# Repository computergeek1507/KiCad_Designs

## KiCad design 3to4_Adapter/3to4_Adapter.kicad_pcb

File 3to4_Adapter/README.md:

# Copyright and Disclaimer
Copyright: Scott Hanson

This documentation describes Open Hardware and is licensed under the CERN OHL v. 1.2.

You may redistribute and modify this documentation under the terms of the CERN OHL v.1.2. (http://ohwr.org/cernohl). This documentation is distributed WITHOUT ANY EXPRESS OR IMPLIED WARRANTY, INCLUDING OF MERCHANTABILITY, SATISFACTORY QUALITY AND FITNESS FOR A PARTICULAR PURPOSE. Please see the CERN OHL v.1.2 for applicable conditions

# 3 to 4 Adapter

Adapter to use Falcon v3 Expansions with the Falcon v4 Controllers. Open source applications were used to create this controller. [KiCad](http://kicad-pcb.org/) was used for the PCB design, and [LibreOffice](https://www.libreoffice.org/) for the documentation.

To order your own PCB upload the gerber.zip file to your favorite PCB manufacture of choice, I personally use [jlcpcb.com](https://jlcpcb.com/).

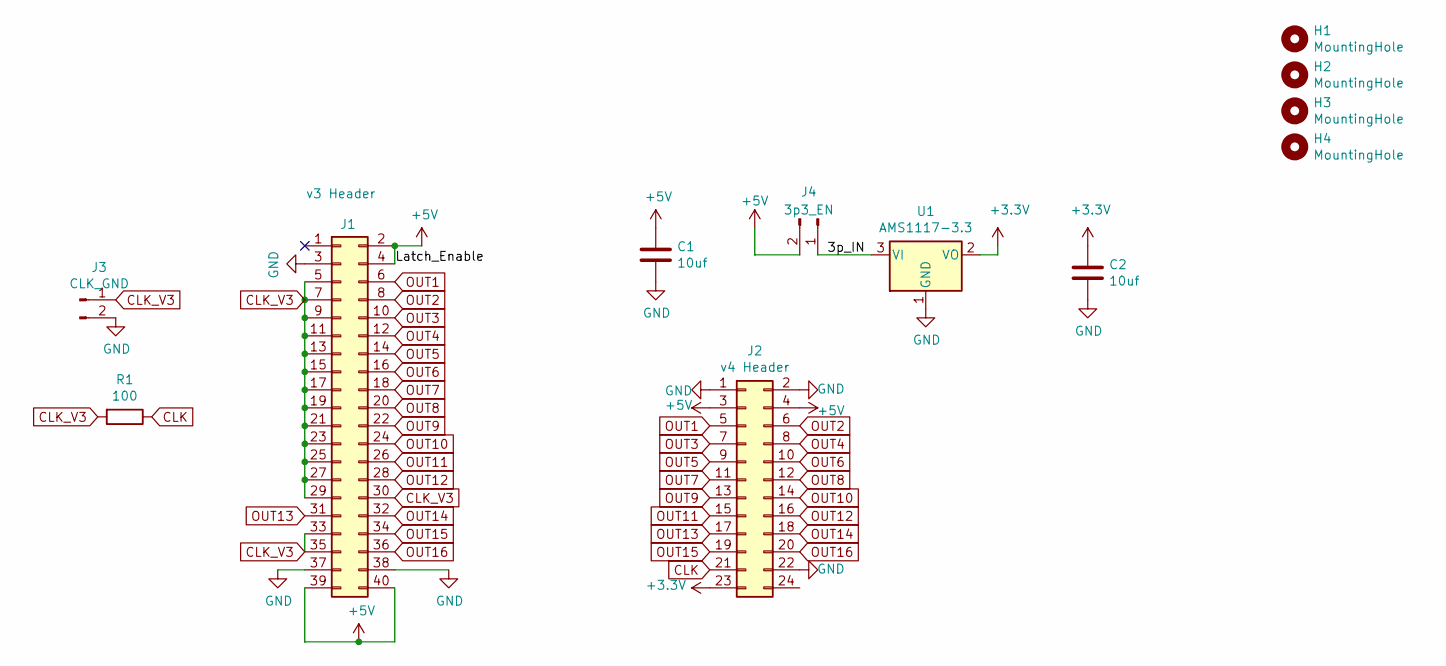
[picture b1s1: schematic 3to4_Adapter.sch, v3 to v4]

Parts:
C1, C2: 10uf; CP_Radial_D5.0mm_P2.00mm; MPN 35ZLG10MEFC5X7; Digi-Key_PN 1189-4000-ND
H1, H2, H3, H4: MountingHole; MountingHole_4.3mm_M4
J1: v3 Header; IDC-Header_2x20_P2.54mm_Vertical; MPN SBH11-PBPC-D20-ST-BK; Digi-Key_PN S9175-ND
J2: v4 Header; OST_302-S241; MPN 302-S241; Digi-Key_PN ED10525-ND
J3: CLK_GND; PinHeader_1x02_P2.54mm_Vertical; MPN 61300211121; Digi-Key_PN 732-5315-ND
J4: 3p3_EN; PinHeader_1x02_P2.54mm_Vertical; MPN 61300211121; Digi-Key_PN 732-5315-ND
R1: 100; R_Axial_DIN0207_L6.3mm_D2.5mm_P7.62mm_Horizontal; MPN CF14JT10K0; Digi-Key_PN CF14JT10K0TR-ND
U1: AMS1117-3.3; SOT-223-3_TabPin2; MPN AP2111H-3.3TRG1; Digi-Key_PN AP2111H-3.3TRG1DICT-ND

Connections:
+3V3: C2.1, J2.23, U1.2 (VO)
+5V: C1.1, J1.2, J1.4, J1.39, J1.40, J2.3, J2.4, J4.2
/3p_IN: J4.1, U1.3 (VI)
CLK: J2.21, R1.1
CLK_V3: J1.5, J1.7, J1.9, J1.11, J1.13, J1.15, J1.17, J1.19, J1.21, J1.23, J1.25, J1.27, J1.29, J1.30, J1.33, J1.35, J3.1, R1.2
GND: C1.2, C2.2, J1.3, J1.37, J1.38, J2.1, J2.2, J2.22, J3.2, U1.1 (GND)
OUT1: J1.6, J2.5
OUT2: J1.8, J2.6
OUT3: J1.10, J2.7
OUT4: J1.12, J2.8
OUT5: J1.14, J2.9
OUT6: J1.16, J2.10
OUT7: J1.18, J2.11
OUT8: J1.20, J2.12
OUT9: J1.22, J2.13
OUT10: J1.24, J2.14
OUT11: J1.26, J2.15
OUT12: J1.28, J2.16
OUT13: J1.31, J2.17
OUT14: J1.32, J2.18
OUT15: J1.34, J2.19
OUT16: J1.36, J2.20

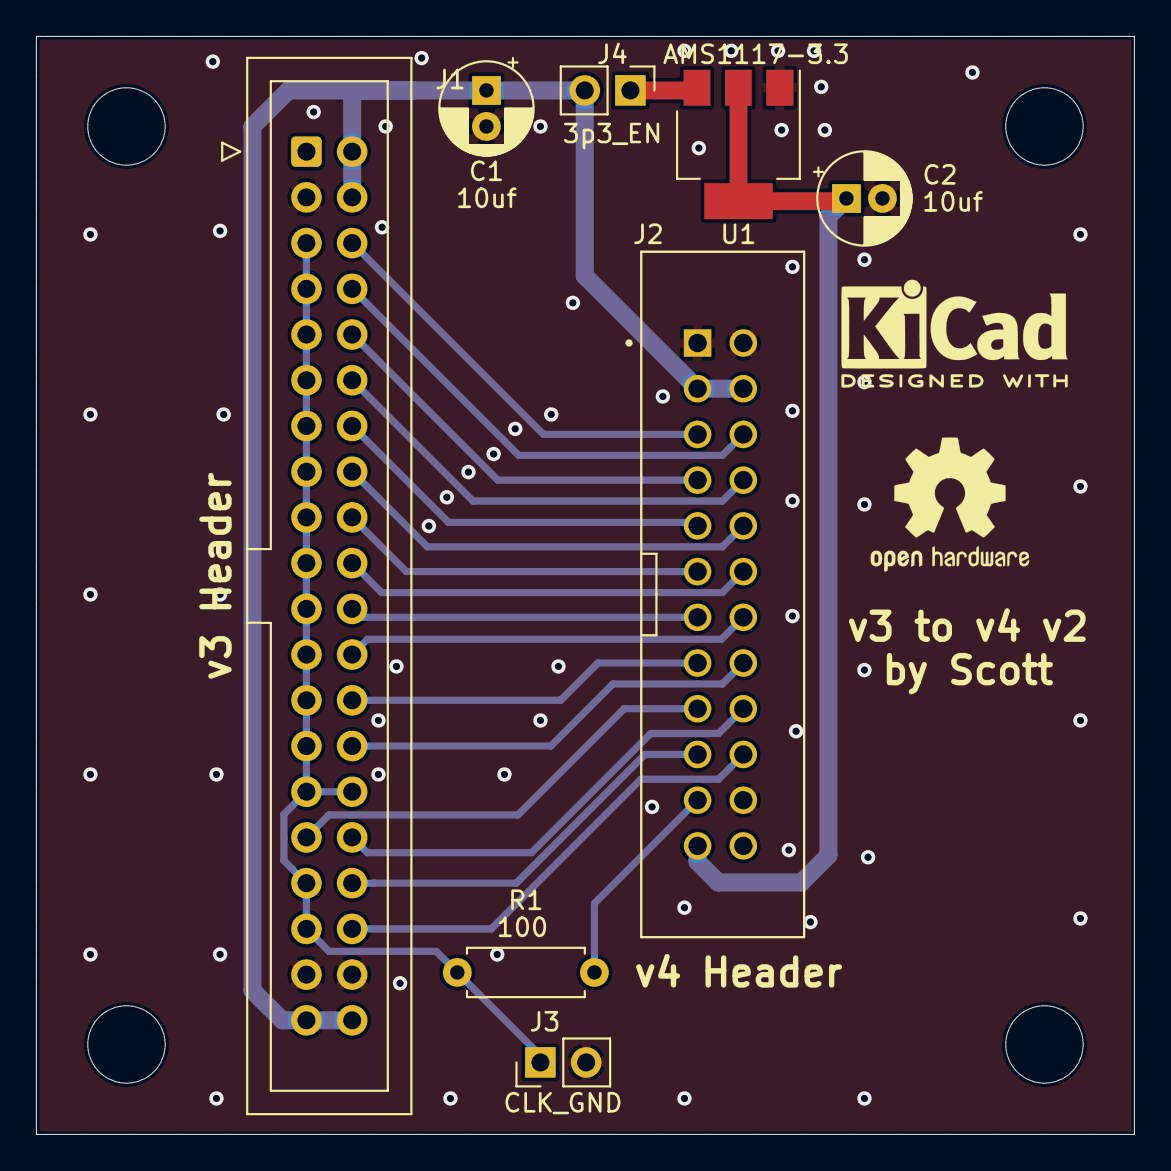
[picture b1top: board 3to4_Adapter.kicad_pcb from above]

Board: 2 copper layers, 61.0 x 61.0 mm, 12 parts (0 on the bottom side), 22 nets.

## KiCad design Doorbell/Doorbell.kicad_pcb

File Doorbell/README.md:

# Copyright and Disclaimer
Copyright: Scott Hanson

This documentation describes Open Hardware and is licensed under the CERN OHL v. 1.2.

You may redistribute and modify this documentation under the terms of the CERN OHL v.1.2. (http://ohwr.org/cernohl). This documentation is distributed WITHOUT ANY EXPRESS OR IMPLIED WARRANTY, INCLUDING OF MERCHANTABILITY, SATISFACTORY QUALITY AND FITNESS FOR A PARTICULAR PURPOSE. Please see the CERN OHL v.1.2 for applicable conditions

# Doorbell

ESP8266 Doorbell Adapter, measures doorbell switch voltage and sends notifications to openHAB. The design was made with all through hole components for easy assembly by most users. Open source applications were used to create this controller. [KiCad](http://kicad-pcb.org/) was used for the PCB design, and [LibreOffice](https://www.libreoffice.org/) for the documentation.

To order your own PCB upload the gerber.zip file to your favorite PCB manufacture of choice, I personally use [jlcpcb.com](https://jlcpcb.com/).

## [Arduino Source Code](https://raw.githubusercontent.com/computergeek1507/arduino/master/ESPMQTT/ESPMQTT.ino)

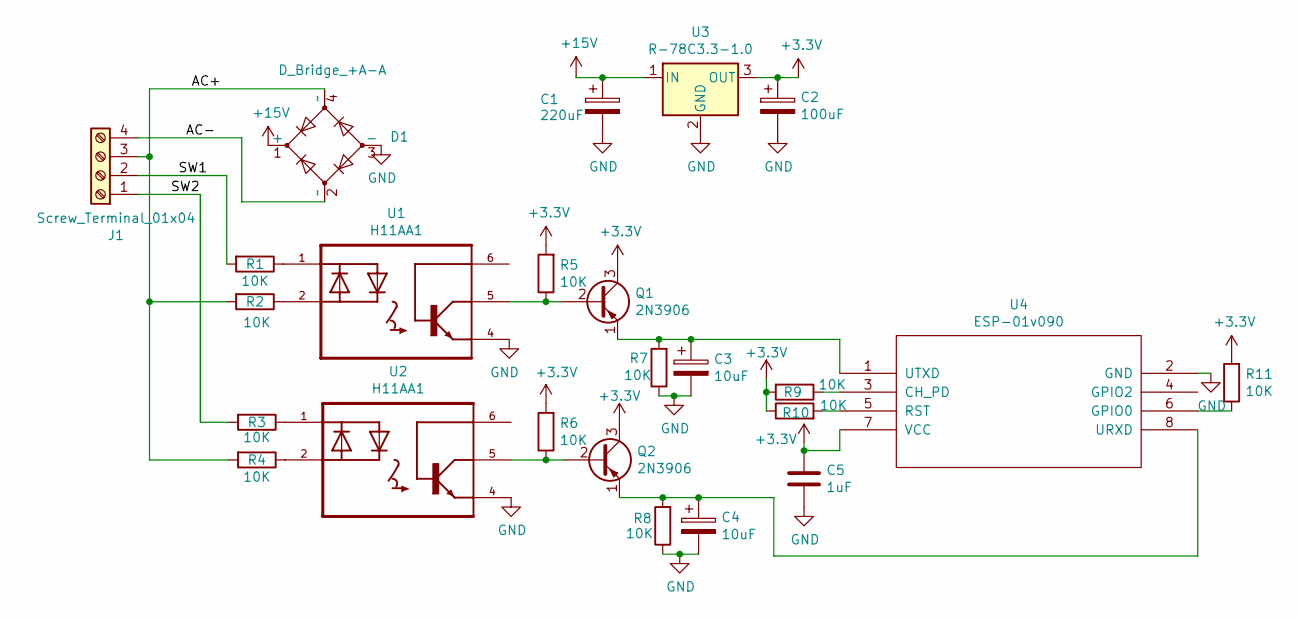
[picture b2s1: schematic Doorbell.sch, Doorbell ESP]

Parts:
C1: 220uF; CP_Radial_D10.0mm_P5.00mm; Manufacture PN ECA-1HM221; Digikey PN P5183-ND
C2: 100uF; CP_Radial_D6.3mm_P2.50mm; Manufacture PN 35ZLH100MEFC6.3X11; Digikey PN 1189-1300-ND
C3, C4: 10uF; CP_Radial_D5.0mm_P2.50mm; Manufacture PN UVR1H100MDD; Digikey PN 493-1103-ND
C5: 1uF; CP_Radial_D5.0mm_P2.50mm; Manufacture PN ESK105M050AC3AA; Digikey PN 399-6596-ND
D1: D_Bridge_+A-A; Diode_Bridge_Round_D8.9mm; Manufacture PN W04G-E4/51; Digikey PN W04G-E4/51GI-ND
J1: Screw_Terminal_01x04; TerminalBlock_Phoenix_MKDS-1,5-4_1x04_P5.00mm_Horizontal; Manufacture PN 1935187; Digikey PN 277-1579-ND
Q1, Q2: 2N3906; TO-92; Manufacture PN 2N3906BU; Digikey PN 2N3906FS-ND
R1, R2, R3, R4, R5, R6, R7, R8, R9, R10, R11: 10K; R_Axial_DIN0204_L3.6mm_D1.6mm_P1.90mm_Vertical; Manufacture PN CF14JT10K0; Digikey PN CF14JT10K0CT-ND
U1, U2: H11AA1; DIP762W50P254L730H410Q6; Manufacture PN H11AA1-X006; Digikey PN H11AA1-X006-ND
U3: R-78C3.3-1.0; Converter_DCDC_RECOM_R-78E-0.5_THT; Manufacture PN OKI-78SR-3.3/1.5-W36-C; Digikey PN 811-2195-5-ND
U4: ESP-01v090; ESP-01; Manufacture PN WRL-13678; Digikey PN 1568-1235-ND

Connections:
+3V3: C2.1, C5.1, Q1.3 (C), Q2.3 (C), R5.2, R6.2, R9.2, R10.1, R11.2, U3.3 (OUT), U4.7 (VCC)
+15V: C1.1, D1.1 (+), U3.1 (IN)
/AC+: D1.4 (~~), J1.3, R2.2, R4.2
/AC-: D1.2 (~~), J1.4
/SW1: J1.2, R1.2
/SW2: J1.1, R3.2
GND: C1.2, C2.2, C3.2, C4.2, C5.2, D1.3 (-), R7.1, R8.1, U1.4 (E), U2.4 (E), U3.2 (GND), U4.2 (GND)
unnamed: C3.1, Q1.1 (E), R7.2, U4.1 (UTXD)
unnamed: C4.1, Q2.1 (E), R8.2, U4.8 (URXD)
unnamed: Q1.2 (B), R5.1, U1.5 (C)
unnamed: Q2.2 (B), R6.1, U2.5 (C)
unnamed: R1.1, U1.1 (A/C)
unnamed: R2.1, U1.2 (C/A)
unnamed: R3.1, U2.1 (A/C)
unnamed: R4.1, U2.2 (C/A)
unnamed: R9.1, U4.3 (CH_PD)
unnamed: R10.2, U4.5 (RST)
unnamed: R11.1, U4.6 (GPIO0)

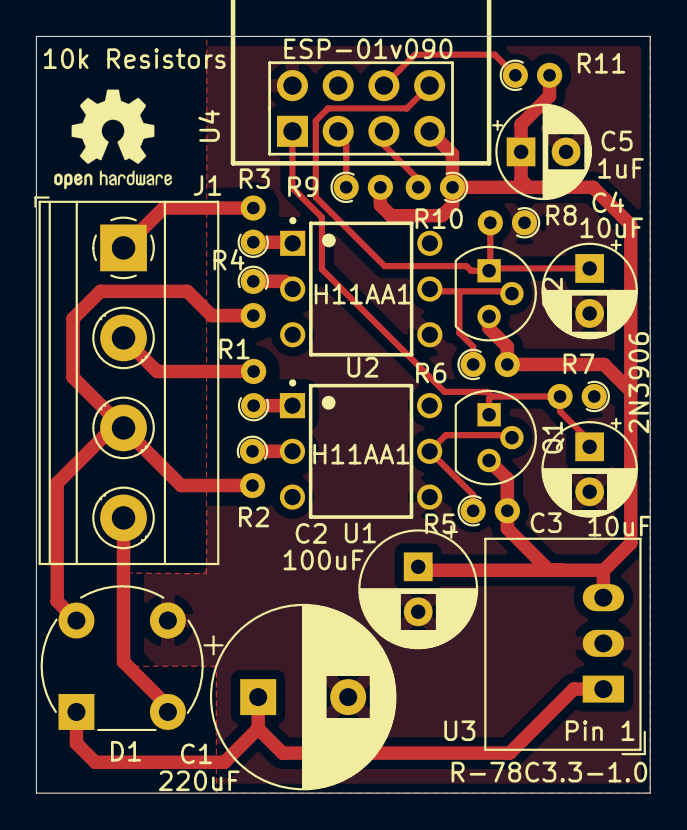
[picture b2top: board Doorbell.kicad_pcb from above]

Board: 2 copper layers, 34.1 x 42.0 mm, 24 parts (0 on the bottom side), 18 nets.

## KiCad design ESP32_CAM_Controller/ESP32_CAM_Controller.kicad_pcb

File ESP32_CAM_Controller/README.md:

# Copyright and Disclaimer
Copyright: Scott Hanson

This documentation describes Open Hardware and is licensed under the CERN OHL v. 1.2.

You may redistribute and modify this documentation under the terms of the CERN OHL v.1.2. (http://ohwr.org/cernohl). This documentation is distributed WITHOUT ANY EXPRESS OR IMPLIED WARRANTY, INCLUDING OF MERCHANTABILITY, SATISFACTORY QUALITY AND FITNESS FOR A PARTICULAR PURPOSE. Please see the CERN OHL v.1.2 for applicable conditions

# ESP32 CAM Controller

4 port Controller breakout for ESP32 CAM Moduke design was made with all through hole components for easy assembly by most users. Open source applications were used to create this controller. [KiCad](http://kicad-pcb.org/) was used for the PCB design, and [LibreOffice](https://www.libreoffice.org/) for the documentation.

To order your own PCB upload the gerber.zip file to your favorite PCB manufacture of choice, I personally use [jlcpcb.com](https://jlcpcb.com/).

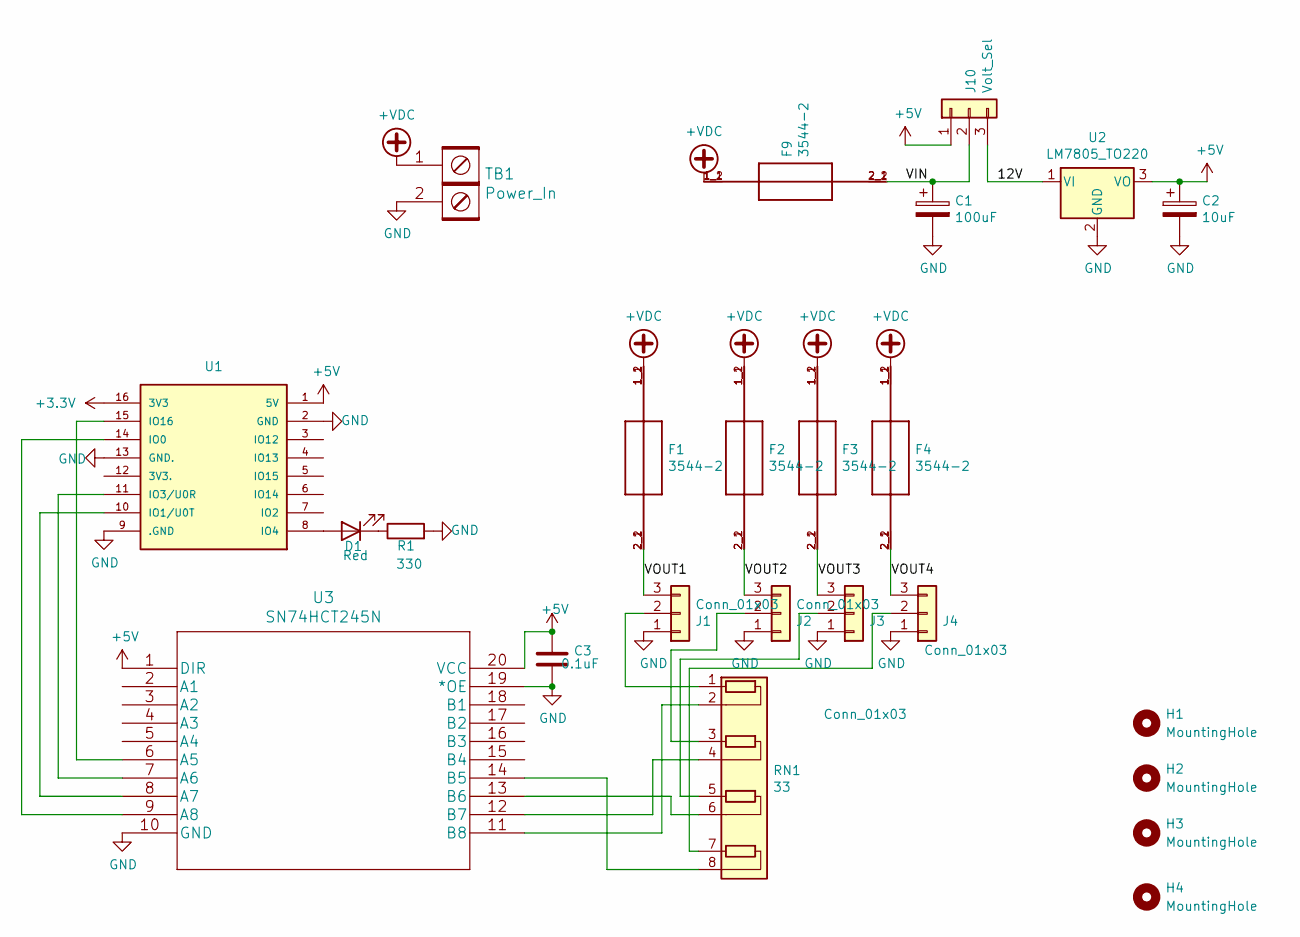
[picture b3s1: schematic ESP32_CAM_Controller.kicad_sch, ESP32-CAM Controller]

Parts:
C1: 100uF; CP_Radial_D8.0mm_P3.50mm
C2: 10uF; CP_Radial_D5.0mm_P2.00mm
C3: 0.1uF; C_Rect_L7.0mm_W2.0mm_P5.00mm
D1: Red; LED_D3.0mm
F1, F2, F3, F4, F9: 3544-2; FUSE_3544-2
H1, H2, H3, H4: MountingHole; MountingHole_3.5mm
J1, J2, J3, J4: Conn_01x03; PhoenixContact_MCV_1,5_3-G-3.5_1x03_P3.50mm_Vertical
J10: Volt_Sel; PinHeader_1x03_P2.54mm_Vertical
R1: 330; R_Axial_DIN0207_L6.3mm_D2.5mm_P7.62mm_Horizontal
RN1: 33; R_Array_SIP8
TB1: Power_In; BARRIER_BLOCK_1ROW_2POS_P8.26MM
U1: ESP32-CAM
U2: LM7805_TO220; TO-220-3_Horizontal_TabDown
U3: SN74HCT245N

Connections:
+3V3: U1.16 (3V3)
+5V: C2.1, C3.1, J10.1, U1.1 (5V), U2.3 (VO), U3.1 (DIR), U3.20 (VCC)
+VDC: F1.1_1 (1), F1.1_2 (1), F2.1_1 (1), F2.1_2 (1), F3.1_1 (1), F3.1_2 (1), F4.1_1 (1), F4.1_2 (1), F9.1_1 (1), F9.1_2 (1), TB1.1
/12V: J10.3, U2.1 (VI)
/VIN: C1.1, F9.2_1 (2), F9.2_2 (2), J10.2
/VOUT1: F1.2_1 (2), F1.2_2 (2), J1.3
/VOUT2: F2.2_1 (2), F2.2_2 (2), J2.3
/VOUT3: F3.2_1 (2), F3.2_2 (2), J3.3
/VOUT4: F4.2_1 (2), F4.2_2 (2), J4.3
GND: C1.2, C2.2, C3.2, J1.1, J2.1, J3.1, J4.1, R1.2, TB1.2, U1.2 (GND), U1.9 (.GND), U1.13 (GND.), U2.2 (GND), U3.10 (GND), U3.19 (*OE)
unnamed: D1.1 (K), R1.1
unnamed: D1.2 (A), U1.8 (IO4)
unnamed: J1.2, RN1.1 (R1.1)
unnamed: J2.2, RN1.3 (R2.1)
unnamed: J3.2, RN1.5 (R3.1)
unnamed: J4.2, RN1.7 (R4.1)
unnamed: U1.15 (IO16), U3.6 (A5)
unnamed: U1.11 (IO3/U0R), U3.7 (A6)
unnamed: U1.10 (IO1/U0T), U3.8 (A7)
unnamed: U1.14 (IO0), U3.9 (A8)
unnamed: RN1.2 (R1.2), U3.11 (B8)
unnamed: RN1.4 (R2.2), U3.12 (B7)
unnamed: RN1.6 (R3.2), U3.13 (B6)
unnamed: RN1.8 (R4.2), U3.14 (B5)

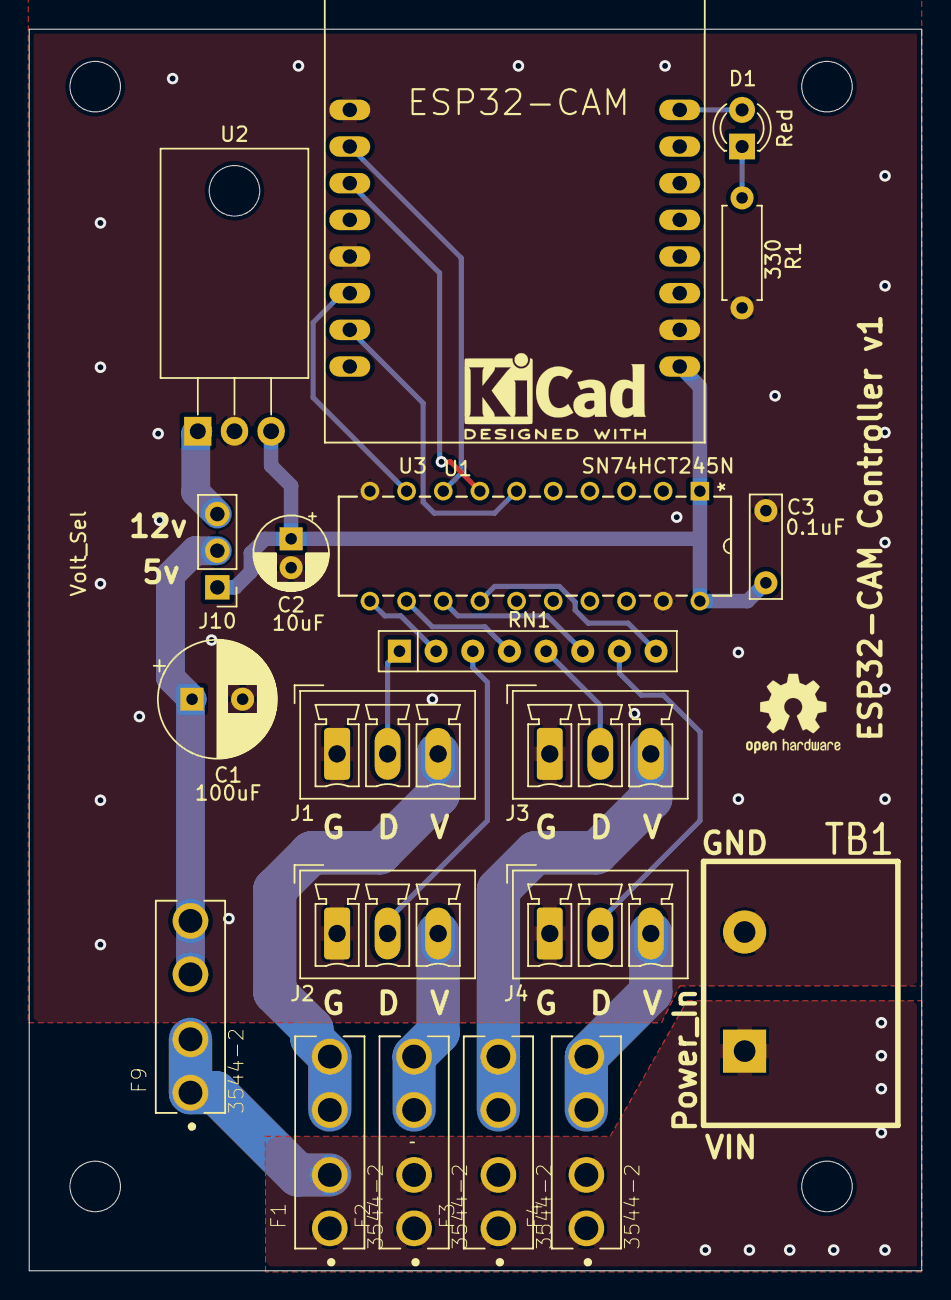
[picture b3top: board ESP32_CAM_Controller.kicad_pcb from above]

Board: 2 copper layers, 61.8 x 86.0 mm, 24 parts (0 on the bottom side), 23 nets.

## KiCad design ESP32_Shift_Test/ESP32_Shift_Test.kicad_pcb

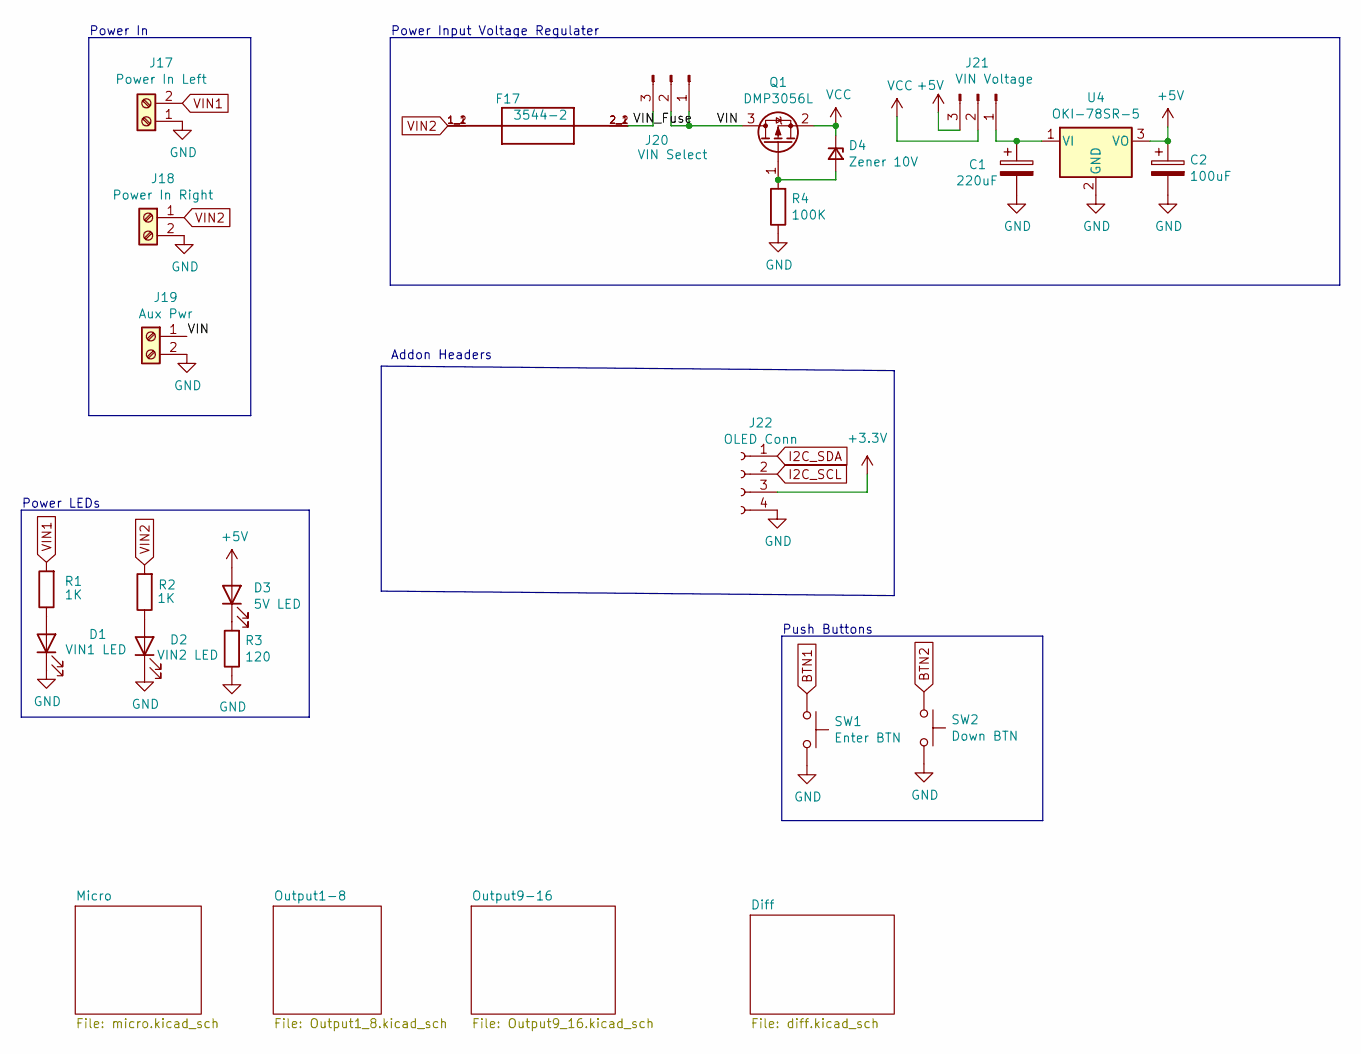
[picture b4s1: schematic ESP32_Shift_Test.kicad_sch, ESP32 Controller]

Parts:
C1: 220uF; CP_Radial_D10.0mm_P5.00mm; MPN ECA-1HM221; Digi-Key_PN P5183-ND
C2: 100uF; CP_Elec_6.3x5.4_Nichicon; MPN UWX1C101MCL1GB; Digi-Key_PN 493-2105-1-ND
D1: VIN1 LED; LED_0603_1608Metric_Pad1.05x0.95mm_HandSolder; MPN LTST-C171GKT; Digi-Key_PN 160-1423-1-ND
D2: VIN2 LED; LED_0603_1608Metric_Pad1.05x0.95mm_HandSolder; MPN LTST-C171GKT; Digi-Key_PN 160-1423-1-ND
D3: 5V LED; LED_0603_1608Metric_Pad1.05x0.95mm_HandSolder; MPN LTST-C171GKT; Digi-Key_PN 160-1423-1-ND
D4: Zener 10V; D_SOD-123; MPN MMSZ5240B-7-F; Digi-Key_PN MMSZ5240B-FDICT-ND
F17: 3544-2; FUSE_3544-2; MPN 3544-2; Digi-Key_PN 36-3544-2-ND
J17: Power In Left; BARRIER_BLOCK_1ROW_2POS_P9.5MM; MPN OSTYK51102030; Digi-Key_PN ED2953-ND
J18: Power In Right; BARRIER_BLOCK_1ROW_2POS_P9.5MM; MPN OSTYK51102030; Digi-Key_PN ED2953-ND
J19: Aux Pwr; PHOENIX_MKDS1_2-3.81; MPN 1727010; Digi-Key_PN 277-1947-ND
J20: VIN Select; PinHeader_1x03_P2.54mm_Vertical; MPN 61300311121; Digi-Key_PN 732-5316-ND
J21: VIN Voltage; PinHeader_1x03_P2.54mm_Vertical; MPN 61300311121; Digi-Key_PN 732-5316-ND
J22: OLED Conn; PinSocket_1x04_P2.54mm_Vertical; MPN PPTC041LFBN-RC; Digi-Key_PN S7002-ND
Q1: DMP3056L; SOT-23; MPN DMP3056L-7; Digi-Key_PN DMP3056L-7DICT-ND
R1, R2: 1K; R_0603_1608Metric_Pad0.98x0.95mm_HandSolder; MPN RNCP0805FTD1K00; Digi-Key_PN RNCP0805FTD1K00CT-ND
R3: 120; R_0603_1608Metric_Pad0.98x0.95mm_HandSolder; MPN RC0805JR-07120RL; Digi-Key_PN 311-120ARCT-ND
R4: 100K; R_0603_1608Metric_Pad0.98x0.95mm_HandSolder; MPN RC0805FR-07100KL; Digi-Key_PN 311-100KCRCT-ND
SW1: Enter BTN; SW_Push_1P1T_NO_6x6mm_H9.5mm; MPN PTS645SL50SMTR92 LFS; Digi-Key_PN CKN9088CT-ND
SW2: Down BTN; SW_Push_1P1T_NO_6x6mm_H9.5mm; MPN PTS645SL50SMTR92 LFS; Digi-Key_PN CKN9088CT-ND
U4: OKI-78SR-5; Converter_DCDC_muRata_OKI-78SR_Horizontal; MPN OKI-78SR-5/1.5-W36-C; Digi-Key_PN 811-2196-5-ND

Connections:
+3V3: J22.3; also elsewhere on the board
+5V: C2.1, D3.2 (A), J21.3, U4.3 (VO); also elsewhere on the board
/VIN: J19.1, J20.1, J20.2, Q1.3 (D)
/VIN_Fuse: F17.2_1 (2), F17.2_2 (2), J20.3
BTN1: SW1.1; also elsewhere on the board
BTN2: SW2.1; also elsewhere on the board
GND: C1.2, C2.2, D1.1 (K), D2.1 (K), J17.1, J18.2, J19.2, J22.4, R3.1, R4.1, SW1.2, SW2.2, U4.2 (GND); also elsewhere on the board
I2C_SCL: J22.2; also elsewhere on the board
I2C_SDA: J22.1; also elsewhere on the board
unnamed: C1.1, J21.1, U4.1 (VI)
unnamed: D1.2 (A), R1.1
unnamed: D2.2 (A), R2.1
unnamed: D3.1 (K), R3.2
unnamed: D4.2 (A), Q1.1 (G), R4.2
VCC: D4.1 (K), J21.2, Q1.2 (S)
VIN1: J17.2, R1.2; also elsewhere on the board
VIN2: F17.1_1 (1), F17.1_2 (1), J18.1, R2.2; also elsewhere on the board

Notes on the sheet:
Power Input Voltage Regulater
Power In
Power LEDs
Push Buttons
Addon Headers

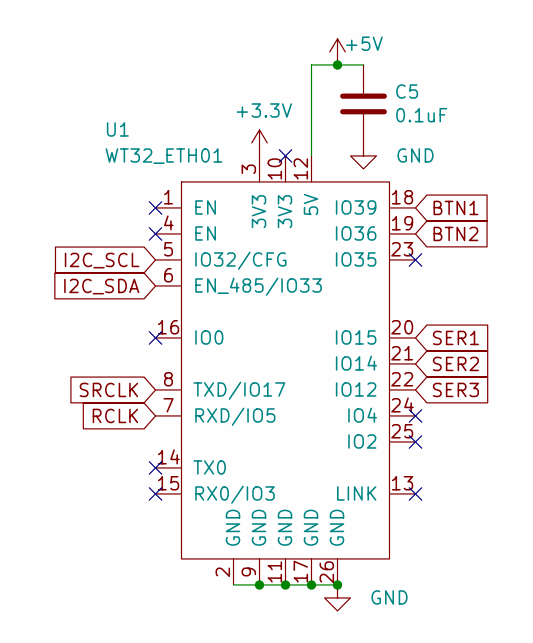
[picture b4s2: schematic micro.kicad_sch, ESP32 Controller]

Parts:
C5: 0.1uF; C_0603_1608Metric_Pad1.08x0.95mm_HandSolder; MPN CL21F104ZBCNNNC; Digi-Key_PN 1276-1007-1-ND
U1: WT32_ETH01

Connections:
+3V3: U1.3 (3V3); also elsewhere on the board
+5V: C5.1, U1.12 (5V); also elsewhere on the board
BTN1: U1.18 (IO39); also elsewhere on the board
BTN2: U1.19 (IO36); also elsewhere on the board
GND: C5.2, U1.2 (GND), U1.9 (GND), U1.11 (GND), U1.17 (GND), U1.26 (GND); also elsewhere on the board
I2C_SCL: U1.5 (IO32/CFG); also elsewhere on the board
I2C_SDA: U1.6 (EN_485/IO33); also elsewhere on the board
RCLK: U1.7 (RXD/IO5); also elsewhere on the board
SER1: U1.20 (IO15); also elsewhere on the board
SER2: U1.21 (IO14); also elsewhere on the board
SER3: U1.22 (IO12); also elsewhere on the board
SER4: U1.24 (IO4)
SRCLK: U1.8 (TXD/IO17); also elsewhere on the board

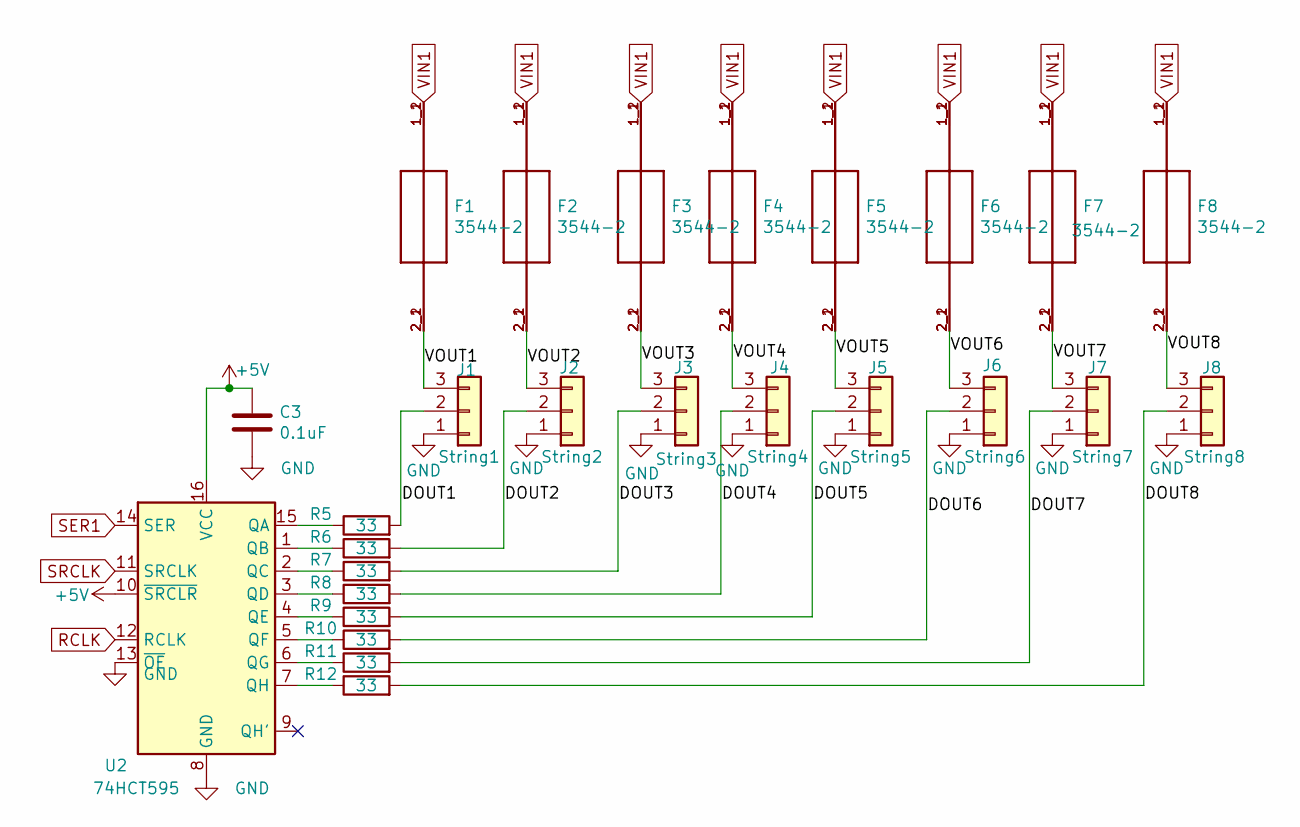
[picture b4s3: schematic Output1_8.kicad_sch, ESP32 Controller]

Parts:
C3: 0.1uF; C_0603_1608Metric_Pad1.08x0.95mm_HandSolder; MPN CL21F104ZBCNNNC; Digi-Key_PN 1276-1007-1-ND
F1, F2, F3, F4, F5, F6, F7, F8: 3544-2; FUSE_3544-2; MPN 3544-2; Digi-Key_PN 36-3544-2-ND
J1: String1; PhoenixContact_MCV_1,5_3-G-3.5_1x03_P3.50mm_Vertical; MPN 1843619/OSTTJ0311530; Digi-Key_PN 277-5737-ND/ED10555-ND
J2: String2; PhoenixContact_MCV_1,5_3-G-3.5_1x03_P3.50mm_Vertical; MPN 1843619/OSTTJ0311530; Digi-Key_PN 277-5737-ND/ED10555-ND
J3: String3; PhoenixContact_MCV_1,5_3-G-3.5_1x03_P3.50mm_Vertical; MPN 1843619/OSTTJ0311530; Digi-Key_PN 277-5737-ND/ED10555-ND
J4: String4; PhoenixContact_MCV_1,5_3-G-3.5_1x03_P3.50mm_Vertical; MPN 1843619/OSTTJ0311530; Digi-Key_PN 277-5737-ND/ED10555-ND
J5: String5; PhoenixContact_MCV_1,5_3-G-3.5_1x03_P3.50mm_Vertical; MPN 1843619/OSTTJ0311530; Digi-Key_PN 277-5737-ND/ED10555-ND
J6: String6; PhoenixContact_MCV_1,5_3-G-3.5_1x03_P3.50mm_Vertical; MPN 1843619/OSTTJ0311530; Digi-Key_PN 277-5737-ND/ED10555-ND
J7: String7; PhoenixContact_MCV_1,5_3-G-3.5_1x03_P3.50mm_Vertical; MPN 1843619/OSTTJ0311530; Digi-Key_PN 277-5737-ND/ED10555-ND
J8: String8; PhoenixContact_MCV_1,5_3-G-3.5_1x03_P3.50mm_Vertical; MPN 1843619/OSTTJ0311530; Digi-Key_PN 277-5737-ND/ED10555-ND
R5, R6, R7, R8, R9, R10, R11, R12: 33; R_0603_1608Metric_Pad0.98x0.95mm_HandSolder; MPN CN34J330CT; LCSC C23140
U2: 74HCT595; SOIC-16_3.9x9.9mm_P1.27mm

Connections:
+5V: C3.1, U2.10 (~SRCLR), U2.16 (VCC); also elsewhere on the board
/Output1-8/DOUT1: J1.2, R5.2
/Output1-8/DOUT2: J2.2, R6.2
/Output1-8/DOUT3: J3.2, R7.2
/Output1-8/DOUT4: J4.2, R8.2
/Output1-8/DOUT5: J5.2, R9.2
/Output1-8/DOUT6: J6.2, R10.2
/Output1-8/DOUT7: J7.2, R11.2
/Output1-8/DOUT8: J8.2, R12.2
/Output1-8/VOUT1: F1.2_1 (2), F1.2_2 (2), J1.3
/Output1-8/VOUT2: F2.2_1 (2), F2.2_2 (2), J2.3
/Output1-8/VOUT3: F3.2_1 (2), F3.2_2 (2), J3.3
/Output1-8/VOUT4: F4.2_1 (2), F4.2_2 (2), J4.3
/Output1-8/VOUT5: F5.2_1 (2), F5.2_2 (2), J5.3
/Output1-8/VOUT6: F6.2_1 (2), F6.2_2 (2), J6.3
/Output1-8/VOUT7: F7.2_1 (2), F7.2_2 (2), J7.3
/Output1-8/VOUT8: F8.2_1 (2), F8.2_2 (2), J8.3
GND: C3.2, J1.1, J2.1, J3.1, J4.1, J5.1, J6.1, J7.1, J8.1, U2.8 (GND), U2.13 (~OE); also elsewhere on the board
unnamed: R5.1, U2.15 (QA)
unnamed: R6.1, U2.1 (QB)
unnamed: R7.1, U2.2 (QC)
unnamed: R8.1, U2.3 (QD)
unnamed: R9.1, U2.4 (QE)
unnamed: R10.1, U2.5 (QF)
unnamed: R11.1, U2.6 (QG)
unnamed: R12.1, U2.7 (QH)
RCLK: U2.12 (RCLK); also elsewhere on the board
SER1: U2.14 (SER); also elsewhere on the board
SRCLK: U2.11 (SRCLK); also elsewhere on the board
VIN1: F1.1_1 (1), F1.1_2 (1), F2.1_1 (1), F2.1_2 (1), F3.1_1 (1), F3.1_2 (1), F4.1_1 (1), F4.1_2 (1), F5.1_1 (1), F5.1_2 (1), F6.1_1 (1), F6.1_2 (1), F7.1_1 (1), F7.1_2 (1), F8.1_1 (1), F8.1_2 (1); also elsewhere on the board

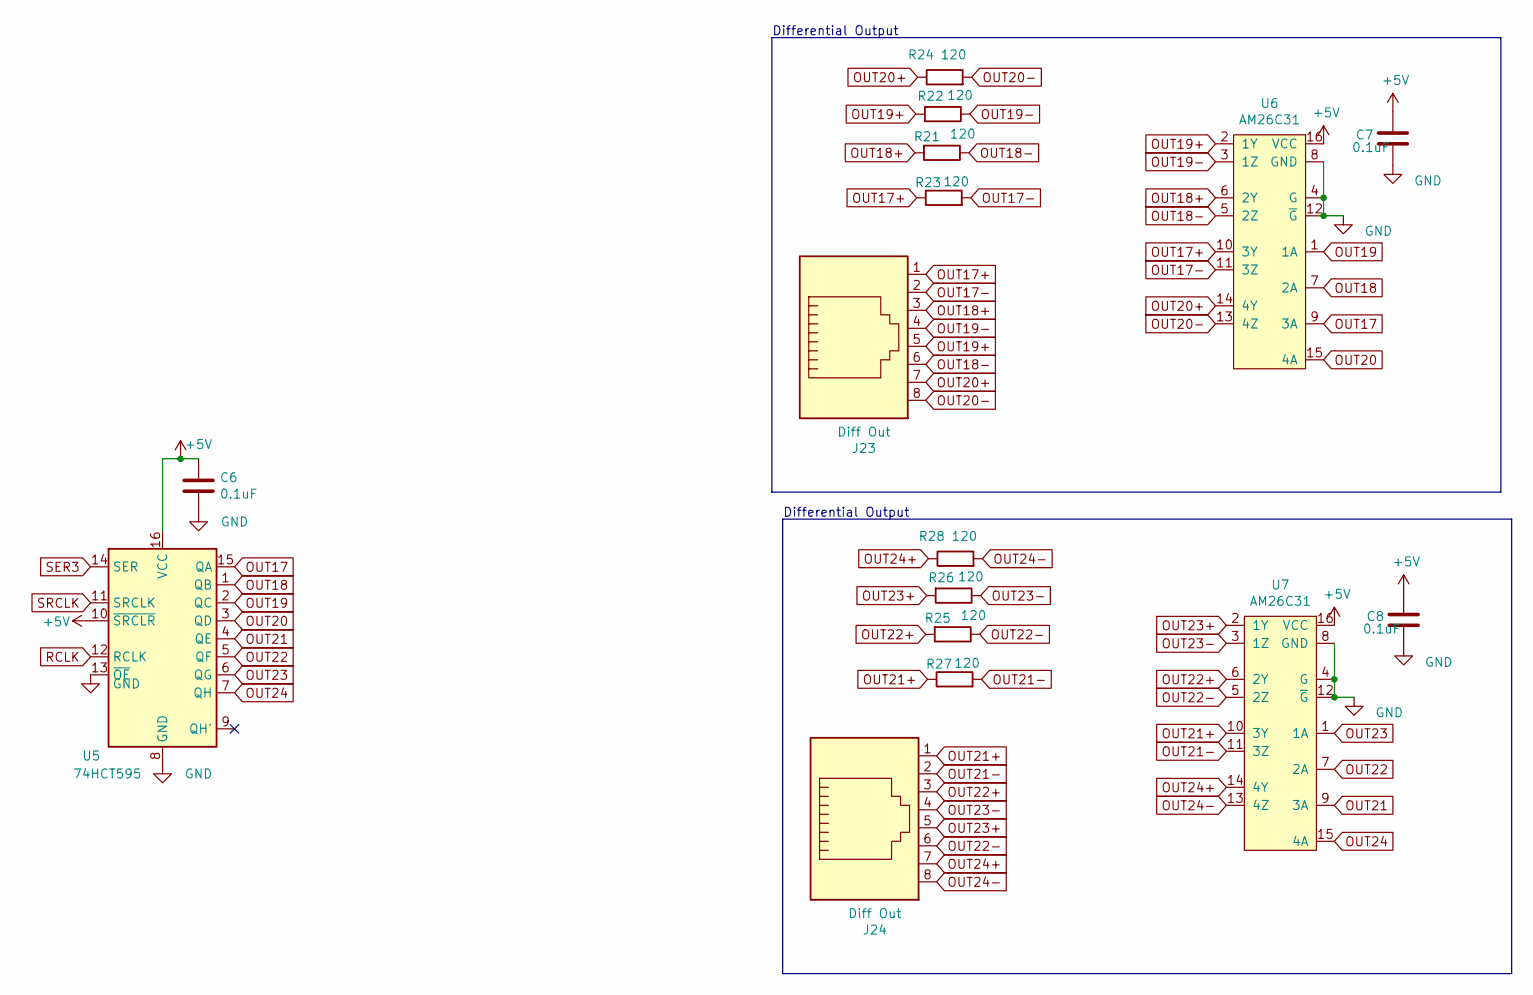
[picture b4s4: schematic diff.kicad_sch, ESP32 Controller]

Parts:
C6: 0.1uF; C_0603_1608Metric_Pad1.08x0.95mm_HandSolder; MPN CL21F104ZBCNNNC; Digi-Key_PN 1276-1007-1-ND
C7, C8: 0.1uF; C_0603_1608Metric_Pad1.08x0.95mm_HandSolder; MPN CL10B104KB8NNWC; Digi-Key_PN 1276-1935-2-ND
J23, J24: Diff Out; RJ45_Amphenol_54602-x08_Horizontal; MPN X05ADIWA1DY1022; Digi-Key_PN AE10392-ND
R21, R22, R23, R24, R25, R26, R27, R28: 120; R_0603_1608Metric_Pad0.98x0.95mm_HandSolder; MPN CRGCQ0603F120R; Digi-Key_PN A129677CT-ND
U5: 74HCT595; SOIC-16_3.9x9.9mm_P1.27mm
U6, U7: AM26C31; SOIC-16_3.9x9.9mm_P1.27mm; MPN AM26C31IDR; Farnell 4975637

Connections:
+5V: C6.1, C7.1, C8.1, U5.10 (~SRCLR), U5.16 (VCC), U6.16 (VCC), U7.16 (VCC); also elsewhere on the board
GND: C6.2, C7.2, C8.2, U5.8 (GND), U5.13 (~OE), U6.4 (G), U6.8 (GND), U6.12 (~G), U7.4 (G), U7.8 (GND), U7.12 (~G); also elsewhere on the board
OUT17: U5.15 (QA), U6.9 (3A)
OUT17+: J23.1, R23.1, U6.10 (3Y)
OUT17-: J23.2, R23.2, U6.11 (3Z)
OUT18: U5.1 (QB), U6.7 (2A)
OUT18+: J23.3, R21.2, U6.6 (2Y)
OUT18-: J23.6, R21.1, U6.5 (2Z)
OUT19: U5.2 (QC), U6.1 (1A)
OUT19+: J23.5, R22.2, U6.2 (1Y)
OUT19-: J23.4, R22.1, U6.3 (1Z)
OUT20: U5.3 (QD), U6.15 (4A)
OUT20+: J23.7, R24.1, U6.14 (4Y)
OUT20-: J23.8, R24.2, U6.13 (4Z)
OUT21: U5.4 (QE), U7.9 (3A)
OUT21+: J24.1, R27.1, U7.10 (3Y)
OUT21-: J24.2, R27.2, U7.11 (3Z)
OUT22: U5.5 (QF), U7.7 (2A)
OUT22+: J24.3, R25.2, U7.6 (2Y)
OUT22-: J24.6, R25.1, U7.5 (2Z)
OUT23: U5.6 (QG), U7.1 (1A)
OUT23+: J24.5, R26.2, U7.2 (1Y)
OUT23-: J24.4, R26.1, U7.3 (1Z)
OUT24: U5.7 (QH), U7.15 (4A)
OUT24+: J24.7, R28.1, U7.14 (4Y)
OUT24-: J24.8, R28.2, U7.13 (4Z)
RCLK: U5.12 (RCLK); also elsewhere on the board
SER3: U5.14 (SER); also elsewhere on the board
SRCLK: U5.11 (SRCLK); also elsewhere on the board

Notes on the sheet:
Differential Output

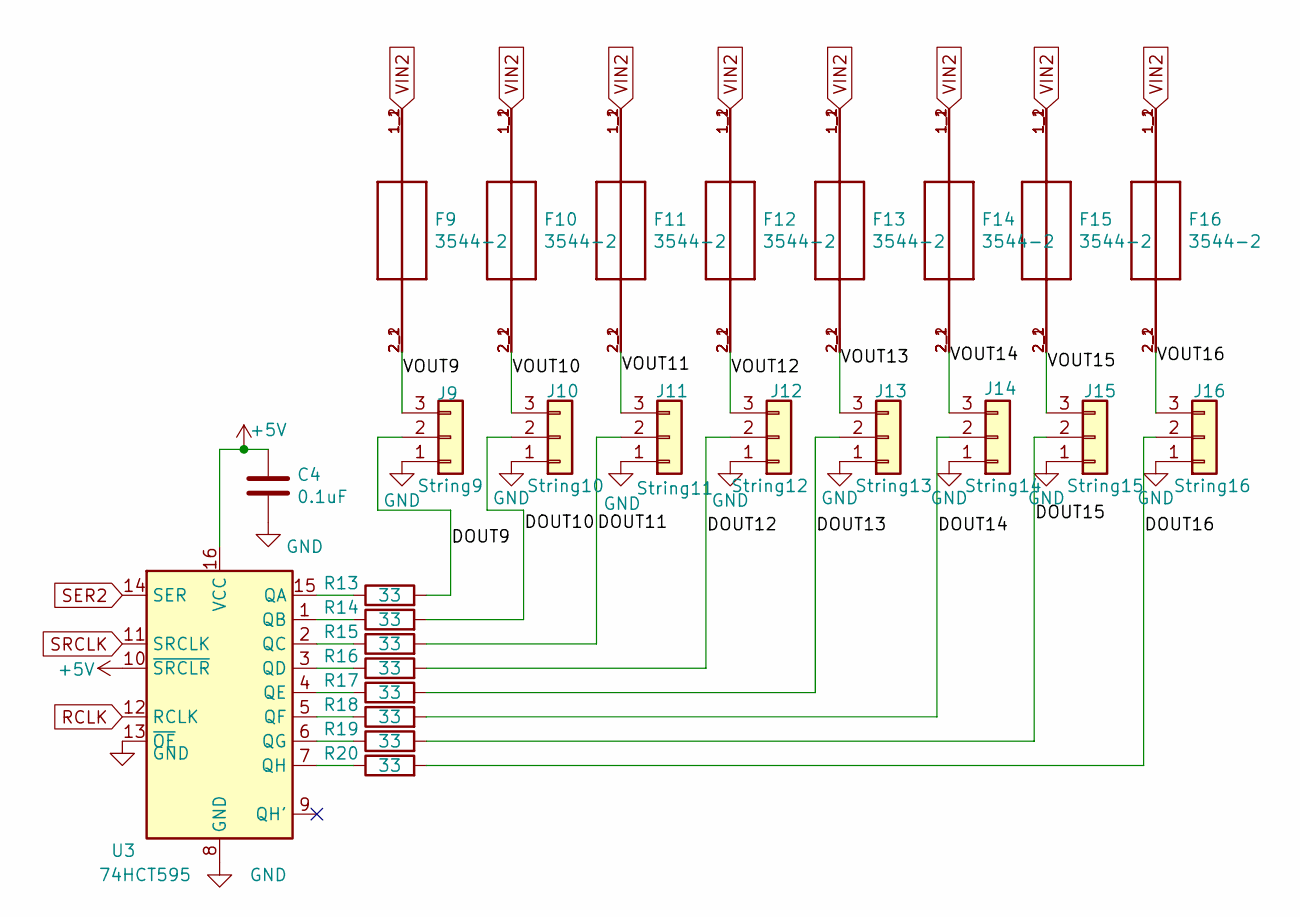
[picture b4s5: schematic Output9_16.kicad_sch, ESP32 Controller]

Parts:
C4: 0.1uF; C_0603_1608Metric_Pad1.08x0.95mm_HandSolder; MPN CL21F104ZBCNNNC; Digi-Key_PN 1276-1007-1-ND
F9, F10, F11, F12, F13, F14, F15, F16: 3544-2; FUSE_3544-2; MPN 3544-2; Digi-Key_PN 36-3544-2-ND
J9: String9; PhoenixContact_MCV_1,5_3-G-3.5_1x03_P3.50mm_Vertical; MPN 1843619/OSTTJ0311530; Digi-Key_PN 277-5737-ND/ED10555-ND
J10: String10; PhoenixContact_MCV_1,5_3-G-3.5_1x03_P3.50mm_Vertical; MPN 1843619/OSTTJ0311530; Digi-Key_PN 277-5737-ND/ED10555-ND
J11: String11; PhoenixContact_MCV_1,5_3-G-3.5_1x03_P3.50mm_Vertical; MPN 1843619/OSTTJ0311530; Digi-Key_PN 277-5737-ND/ED10555-ND
J12: String12; PhoenixContact_MCV_1,5_3-G-3.5_1x03_P3.50mm_Vertical; MPN 1843619/OSTTJ0311530; Digi-Key_PN 277-5737-ND/ED10555-ND
J13: String13; PhoenixContact_MCV_1,5_3-G-3.5_1x03_P3.50mm_Vertical; MPN 1843619/OSTTJ0311530; Digi-Key_PN 277-5737-ND/ED10555-ND
J14: String14; PhoenixContact_MCV_1,5_3-G-3.5_1x03_P3.50mm_Vertical; MPN 1843619/OSTTJ0311530; Digi-Key_PN 277-5737-ND/ED10555-ND
J15: String15; PhoenixContact_MCV_1,5_3-G-3.5_1x03_P3.50mm_Vertical; MPN 1843619/OSTTJ0311530; Digi-Key_PN 277-5737-ND/ED10555-ND
J16: String16; PhoenixContact_MCV_1,5_3-G-3.5_1x03_P3.50mm_Vertical; MPN 1843619/OSTTJ0311530; Digi-Key_PN 277-5737-ND/ED10555-ND
R13, R14, R15, R16, R17, R18, R19, R20: 33; R_0603_1608Metric_Pad0.98x0.95mm_HandSolder; MPN CN34J330CT; LCSC C23140
U3: 74HCT595; SOIC-16_3.9x9.9mm_P1.27mm

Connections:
+5V: C4.1, U3.10 (~SRCLR), U3.16 (VCC); also elsewhere on the board
/Output9-16/DOUT9: J9.2, R13.2
/Output9-16/DOUT10: J10.2, R14.2
/Output9-16/DOUT11: J11.2, R15.2
/Output9-16/DOUT12: J12.2, R16.2
/Output9-16/DOUT13: J13.2, R17.2
/Output9-16/DOUT14: J14.2, R18.2
/Output9-16/DOUT15: J15.2, R19.2
/Output9-16/DOUT16: J16.2, R20.2
/Output9-16/VOUT9: F9.2_1 (2), F9.2_2 (2), J9.3
/Output9-16/VOUT10: F10.2_1 (2), F10.2_2 (2), J10.3
/Output9-16/VOUT11: F11.2_1 (2), F11.2_2 (2), J11.3
/Output9-16/VOUT12: F12.2_1 (2), F12.2_2 (2), J12.3
/Output9-16/VOUT13: F13.2_1 (2), F13.2_2 (2), J13.3
/Output9-16/VOUT14: F14.2_1 (2), F14.2_2 (2), J14.3
/Output9-16/VOUT15: F15.2_1 (2), F15.2_2 (2), J15.3
/Output9-16/VOUT16: F16.2_1 (2), F16.2_2 (2), J16.3
GND: C4.2, J9.1, J10.1, J11.1, J12.1, J13.1, J14.1, J15.1, J16.1, U3.8 (GND), U3.13 (~OE); also elsewhere on the board
unnamed: R13.1, U3.15 (QA)
unnamed: R14.1, U3.1 (QB)
unnamed: R15.1, U3.2 (QC)
unnamed: R16.1, U3.3 (QD)
unnamed: R17.1, U3.4 (QE)
unnamed: R18.1, U3.5 (QF)
unnamed: R19.1, U3.6 (QG)
unnamed: R20.1, U3.7 (QH)
RCLK: U3.12 (RCLK); also elsewhere on the board
SER2: U3.14 (SER); also elsewhere on the board
SRCLK: U3.11 (SRCLK); also elsewhere on the board
VIN2: F9.1_1 (1), F9.1_2 (1), F10.1_1 (1), F10.1_2 (1), F11.1_1 (1), F11.1_2 (1), F12.1_1 (1), F12.1_2 (1), F13.1_1 (1), F13.1_2 (1), F14.1_1 (1), F14.1_2 (1), F15.1_1 (1), F15.1_2 (1), F16.1_1 (1), F16.1_2 (1); also elsewhere on the board

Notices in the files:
parts and their libraries:
Copyright 2016 Accelerated Designs. All rights reserved.
